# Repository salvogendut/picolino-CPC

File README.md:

# Picolino CPC

A new combined expansion board for the Amstrad CPC, built around a
**Raspberry Pi Pico 2 / RP2350**.

Development branch: `design/pico2-prototype`.
[Implementation issue #1](https://github.com/salvogendut/picolino-CPC/issues/1).

Revision A0 is a **150 × 120 mm, two-layer prototype**. The image is a KiCad
render of the routed design. The W5100S model is a simplified envelope; the
external CH376 module, ribbon cables, shunts and battery cell are not shown.

## Design files

- [KiCad 10 project](hardware/kicad/picolino-cpc.kicad_pro),
  [schematic](hardware/kicad/picolino-cpc.kicad_sch) and
  [PCB](hardware/kicad/picolino-cpc.kicad_pcb).
- [Five-page schematic PDF](hardware/kicad/picolino-cpc-schematic.pdf),
  [BOM](hardware/kicad/bom.csv) and [top assembly drawing](hardware/kicad/picolino-cpc-assembly.svg).
- [3D perspective](docs/images/picolino-cpc-3d.png) and
  [top view](docs/images/picolino-cpc-top.png).
- [Connections, jumper settings and assembly notes](hardware/README.md).

Open the project after cloning the whole repository. Symbols, footprints and
3D models use project-relative paths and are included locally.

| Function | Selected hardware | Intended connection |
| --- | --- | --- |
| ROM emulation | Socketed Pico 2 | CPC memory bus through level translation |
| USB storage | CH376 parallel USB host module | CPC I/O bus, `FE80` / `FE81` |
| Ethernet | **W5100S** parallel module | CPC I/O bus, `FD20`–`FD23` |
| Mouse | PIC16F84A and 74HCT244 | Cyboard mouse interface, `FD10` |
| RTC | Ricoh RP5C01, DIP-18, and CR2032 holder | New nibble-wide RTC interface |
| Address decoding | GAL20V8 and 74HCT21 | Full 16-bit peripheral decoding |

This is the combined-board project. The earlier Cyboard wired POC and its
unfinished RP2040-only carrier are references, not the Picolino PCB.

## Current state

The repository contains the component/compatibility specification, source
provenance, checked interface data, a revised GAL design, the existing PIC mouse
firmware and CH376 diagnostic, and an RP2350-native bus-monitor firmware target.
The monitor deliberately leaves every CPC-facing GPIO as an input. It is a
bring-up tool, **not the completed ROM emulator**.

Revision A uses the reference projects' parallel modules and the original RP5C01
in DIP-18, as confirmed on 2026-10-07. The complete schematic and routed PCB are
included. **This is an untested prototype, not a fabrication release.** Physical
module fit, power sequencing, RTC calibration and CPC bus timing still require
bench validation. Keep both ROM-enable shunts removed with the monitor firmware.
Track implementation in [the design plan](docs/design-plan.md), and read
[the architecture](docs/architecture.md) before connecting hardware.

## Compatibility

- Ethernet and mouse retain the Cyboard register interfaces. Physical regression
  tests remain necessary.
- CH376 uses its own USB-storage protocol; it does not emulate a CF/ATA drive.
- RP5C01 is **not register-compatible with DS12887/Symbiface RTC software**.
  The new driver must read/write 4-bit registers, select banks and handle BCD.
- The inherited PIC firmware speaks **PS/2 mouse protocol**. A USB-shaped mouse
  connector only works with mice supporting that protocol; it is not USB HID.
- Pico 2 needs an RP2350 firmware build. The old RP2040 UF2 and custom linker
  script must not be reused as Pico 2 firmware.

## Software checks

```sh
python3 tools/build_legacy.py --galasm /path/to/galasm --rasm /path/to/rasm
python3 tests/test_decode.py
python3 tests/test_interfaces.py
python3 tests/test_ch376.py   # requires z80==1.0.0
python3 tools/check_hardware.py  # checks the exported KiCad netlist
```

Build the Pico 2 monitor using Pico SDK 2.2.0 and an Arm embedded toolchain:

```sh
cmake -S firmware/pico2 -B build/pico2 -DPICO_BOARD=pico2 \
  -DPICO_SDK_PATH=/path/to/pico-sdk \
  -DPICO_TOOLCHAIN_PATH=/path/to/arm-gnu-toolchain
cmake --build build/pico2 --parallel
```

Use the Arm Cortex-M33 target for this initial revision. Keep hardware ROM enable
off when using the monitor: it never supplies CPC ROM data. USB serial at the
Pico's own USB connector reports bus snapshots and the actual system clock.
The CH376's USB host connector is separate.

See [sources and licensing](docs/sources.md). No CPC OS/BASIC ROMs are included.
Recorded tool versions, results and remaining checks are in
[validation.md](docs/validation.md).

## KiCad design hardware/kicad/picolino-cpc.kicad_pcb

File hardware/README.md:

# Picolino CPC revision A0 hardware

The editable [KiCad 10 project](kicad/picolino-cpc.kicad_pro) contains a cover
sheet and four circuit sheets: bus/power, Pico ROM interface, Ethernet/mouse and
RTC. The PCB is 150 × 120 mm, two copper layers, 1.6 mm nominal thickness, with
four 3.2 mm non-plated mounting holes on a 142 × 112 mm rectangle. Nominal signal
tracks are 0.25 mm; power distribution is 0.80 mm, with pad escapes where needed.
The project minimum is 0.20 mm track/clearance and 0.30 mm drilled vias; routed
vias use 0.70/0.35 mm diameter/drill. Ground pours occupy both layers.

The preview uses Raspberry Pi's official Pico 2 STEP model, local KiCad models,
and an approximate W5100S module envelope. The W5100S connector pad positions
and outline come from Cyboard's EAGLE package; its component heights are
illustrative. Check the actual selected module before manufacture. CH376 is an
external module connected to J2, so it is not included in the rendering.

## Connectors and settings

| Reference | Connection / setting |
| --- | --- |
| J1 | CPC 50-contact expansion through a short, straight-through 50-way ribbon. Pin 1 is marked; check contact numbering at both ends. |
| J2 | Reference parallel CH376 module, 2 × 8 at 2.54 mm, via short straight-through ribbon. Pin 5 supplies fused 5 V; pin 7 is unused. |
| U8 | Cyboard parallel W5100S module, two 1 × 16 sockets, 2.54 mm pitch and 25.4 mm row spacing. RJ45 faces the top edge. |
| U1 | Original Pico 2 with fitted headers; two 1 × 20 sockets, 17.78 mm row spacing. Micro-USB faces the top edge. |
| J4 | PS/2-compatible mouse in a USB-A-shaped socket. This is not a USB HID host. |
| J3 | External **regulated 5 V**: pin 1 positive, pin 2 ground. |
| JP1 | **One shunt only:** 1–2 selects CPC power; 2–3 selects external power. Change only with all power disconnected. |
| JP2 | Both shunts removed: internal CPC ROM and input-only monitor. Fit 1–2 and 3–4 together only with working RP2350 ROM firmware. |
| BT1 | CR2032, positive face up, Keystone 103 holder. No charging circuit. |
| TP1 | RTC ALARM output for calibration/diagnostics; not connected to CPC interrupt. |

J1 contact 40 (`BUSRESET_N`) and contact 41 (`RESET_N`) are separate signals.
The exact contact maps are in [interfaces.json](interfaces.json) and the PDF.
Module orientation must be checked by pin number, not ribbon wire colour.
An SPI-only WIZ810Sio cannot be fitted to U8.

External 5 V is preferred during USB-drive bring-up. JP1 prevents the selected
external supply from feeding CPC 5 V; D1 prevents Pico USB from feeding the
board supply. With external power selected, power the CPC before the board and
turn the board off first: direct peripheral buses are not hot-swap interfaces.
Q1 also disables the Pico translators when CPC 5 V is absent. Measure the full
Pico/module/mouse/USB load before selecting CPC power. F1 protects the CH376
branch, not the whole board; its 500 mA hold rating is not a regulated USB current
limit. Validate USB inrush and voltage drop with the intended drive.

## Assembly

Use the [BOM](kicad/bom.csv) with the [assembly drawing](kicad/picolino-cpc-assembly.svg)
and [schematic PDF](kicad/picolino-cpc-schematic.pdf). The standard passives are
0805; translators are SOIC-20W, supervisor SOIC-8 and Q1 SOT-23. The GAL, PIC,
HCT logic and RTC use DIP sockets. Fit the exact SN74CB3T3245 level-translating
part; an ordinary HC245 or a similarly named bus switch is not equivalent.

Program U2 from the project's GAL source and U9 with the preserved Cyboard PIC
HEX. The Pico firmware currently supplied is an input-only monitor. Leave JP2
open; enabling ROMDIS without a working ROM service prevents normal CPC boot.
Fit one power-selection shunt only. Module sockets and removable shunts are
assembly items in addition to the populated-board BOM. J1 pin 2, U2 pin 12 and
the ground pads of C4/C5 use solid plane connections because surrounding traces
leave insufficient thermal spokes. These joints need adequate soldering heat;
other plane-connected component pads retain thermal reliefs.

U13 is **MAX690AESA+**, with VOUT on pin 1 and battery input on pin 8. Its power
fail output drives the active-high RTC CS input low during backup. WDI is open
to disable the watchdog, PFI is grounded, and PFO is unused. Only the RTC is
battery powered. R20–R30 bias the RTC's bus pins to ground when the board is off.

The original **RP5C01** uses a different oscillator network from RP5C01A:
32.768 kHz crystal, 100 kΩ series resistor, 30 pF at the crystal/resistor node,
56 pF at OSCOUT and an adjustable input load. Use C0G fixed capacitors. Set and
calibrate CV1 using ALARM output mode, avoiding a probe on the crystal pins.
Validate oscillation, trim range, supply transitions and retention current on
the assembled board. The selected crystal needs leads formed to the PCB pitch;
see its BOM note. Verify sourced trimmer and module dimensions before ordering.

## Editing and validation

The native CAD is the reviewable design. `tools/pcb_design.py` records the
circuit and placement; **running `--pcb` replaces all routing**. Preserve manual
edits before regeneration. `--schematic` also regenerates project constraints,
BOM and manifest. `--libraries` needs the KiCad library directory and preserves
the separately supplied Pico STEP model. The module envelope is generated by
`tools/module_model.py`. Routing uses a local Freerouting DSN/SES exchange through
`tools/pcb_route.py`; it does not upload the design to a routing service.
`tools/pcb_finish.py` records the post-route width, edge-clearance, ground-pad
and model corrections for this revision. Its removed-stub UUID belongs to this
particular routing result; review and rerun checks after any new routing pass.

Run from the repository root using KiCad 10:

```sh
kicad-cli sch export netlist hardware/kicad/picolino-cpc.kicad_sch \
  --format kicadxml --output hardware/kicad/checks/netlist.xml
kicad-cli sch erc hardware/kicad/picolino-cpc.kicad_sch --format json \
  --output hardware/kicad/checks/erc.json --exit-code-violations
python3 tools/check_hardware.py
kicad-cli pcb drc hardware/kicad/picolino-cpc.kicad_pcb --format json \
  --output hardware/kicad/checks/drc.json --schematic-parity \
  --refill-zones --save-board --exit-code-violations
```

See [validation](../docs/validation.md) for results and pending bench work,
and [library provenance](kicad/libraries/README.md) for copied assets. No board
has been manufactured or electrically tested. Gerbers are not a release
deliverable at this stage; export them only after reviewing the actual modules,
assembly choices and the outstanding prototype checks.

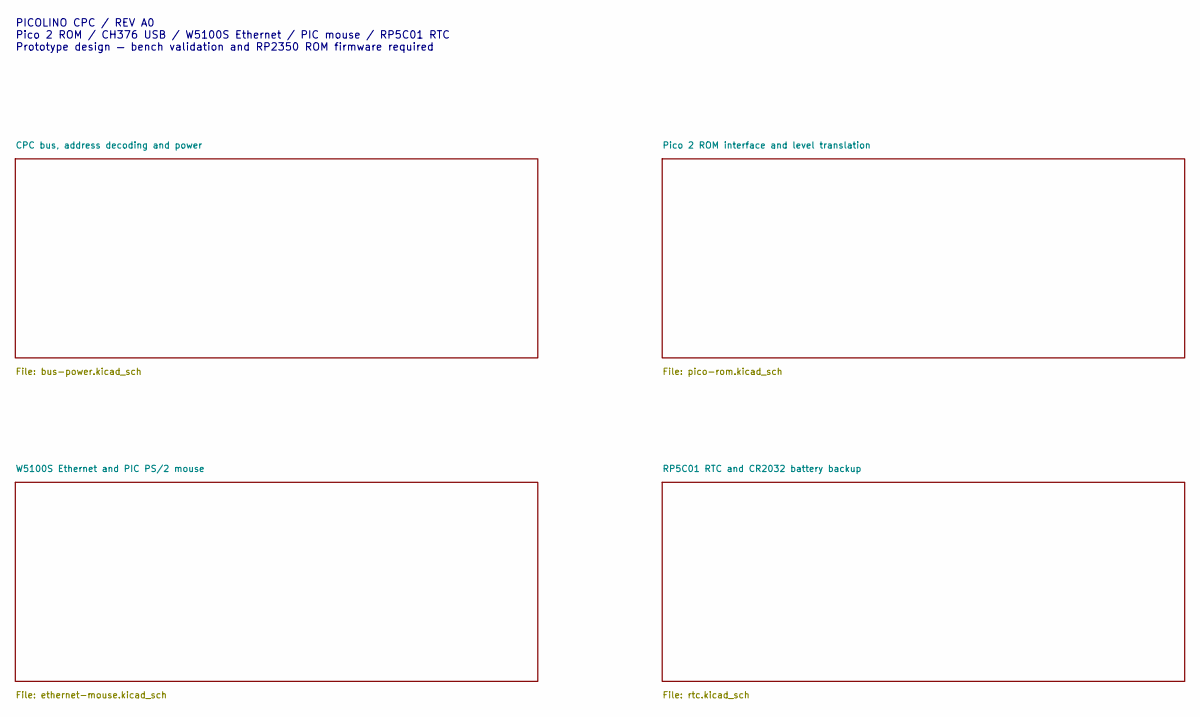
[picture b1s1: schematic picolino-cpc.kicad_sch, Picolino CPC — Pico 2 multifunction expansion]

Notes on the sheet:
PICOLINO CPC / REV A0 Pico 2 ROM / CH376 USB / W5100S Ethernet / PIC mouse / RP5C01 RTC Prototype design — bench validation and RP2350 ROM firmware required

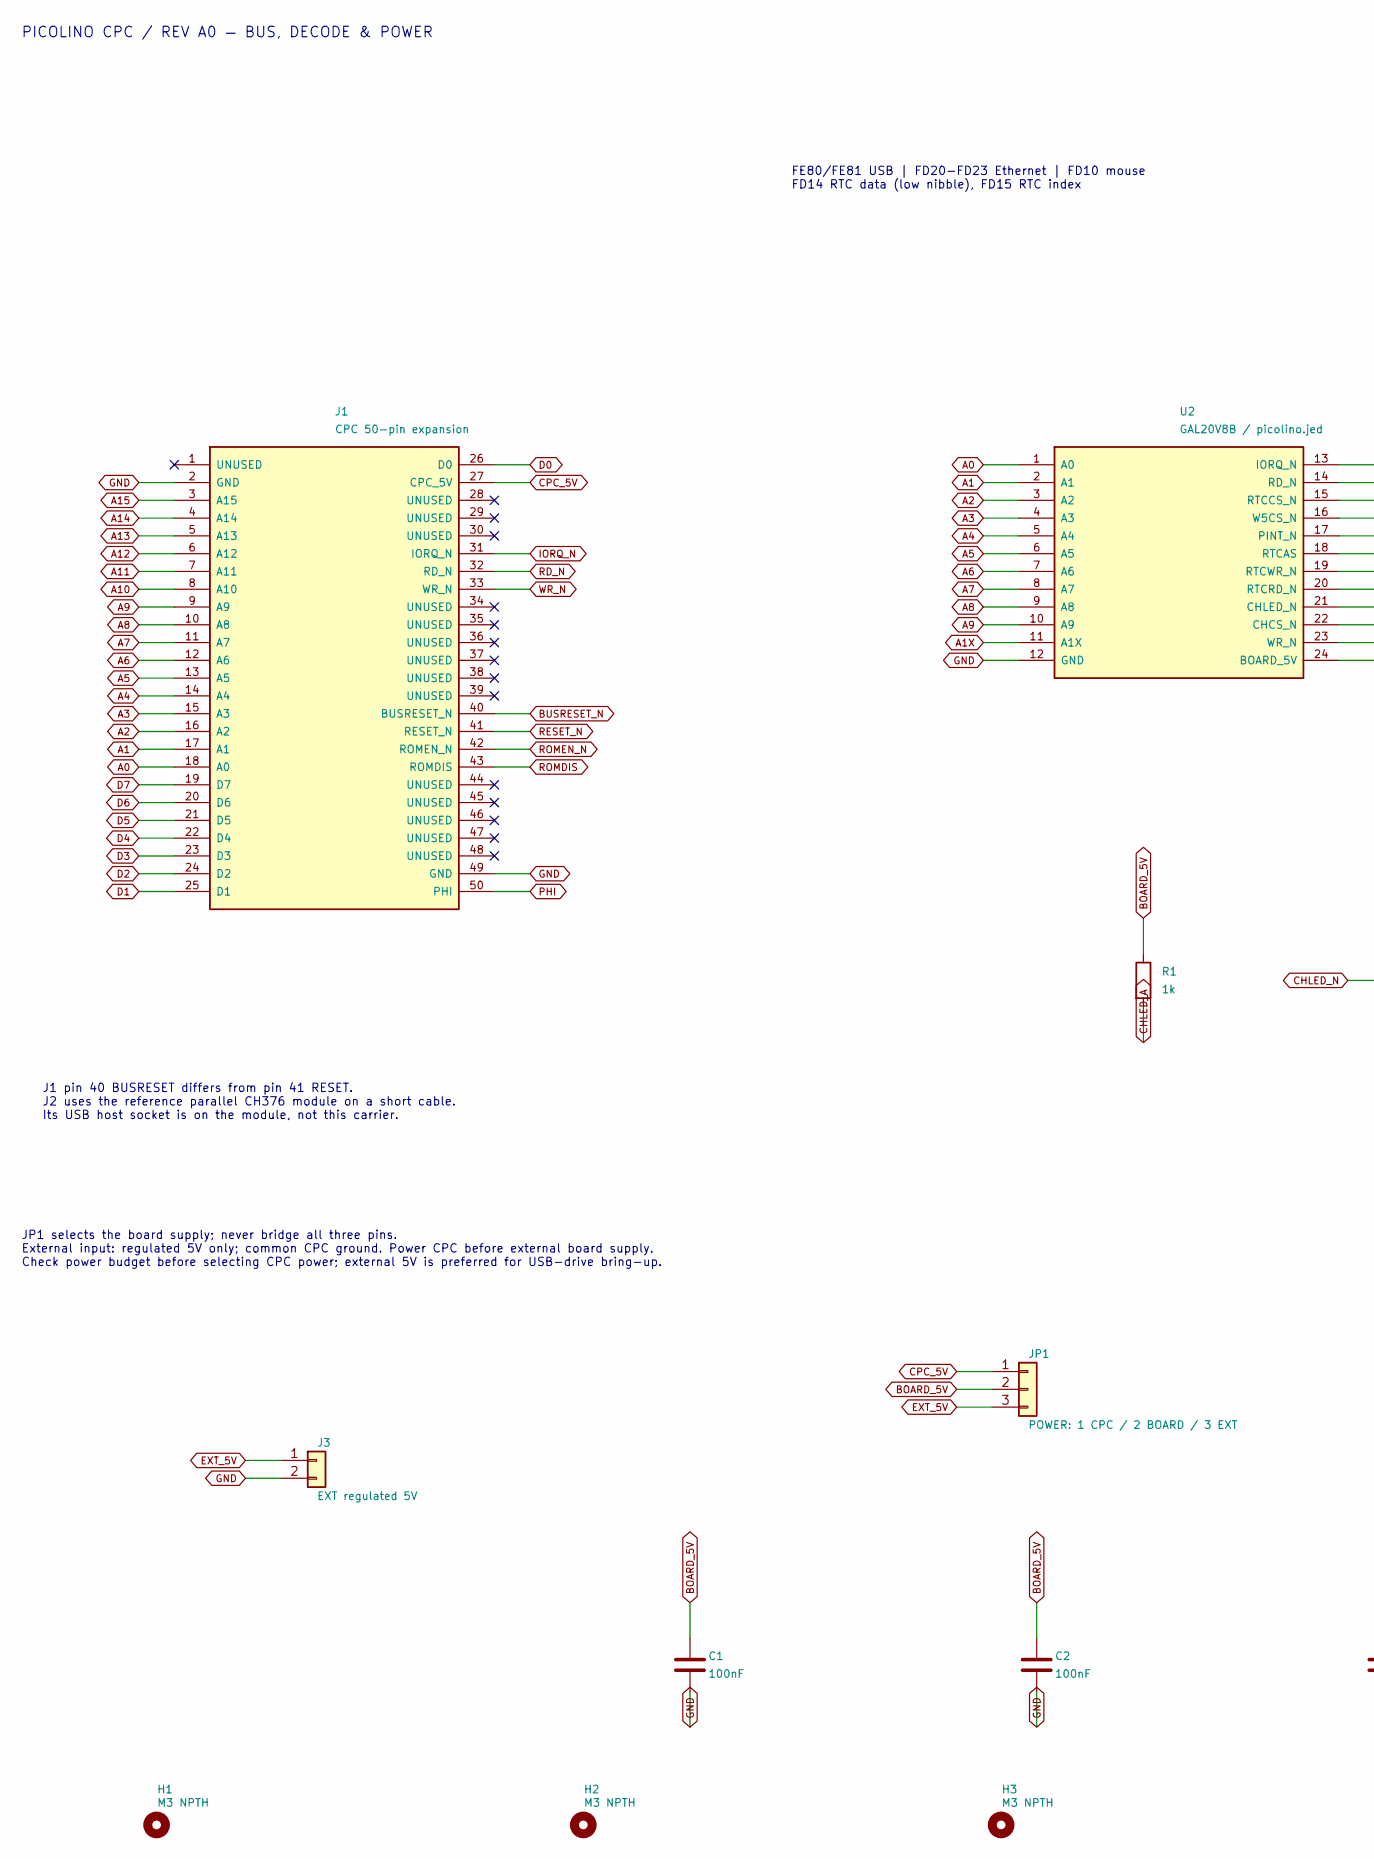
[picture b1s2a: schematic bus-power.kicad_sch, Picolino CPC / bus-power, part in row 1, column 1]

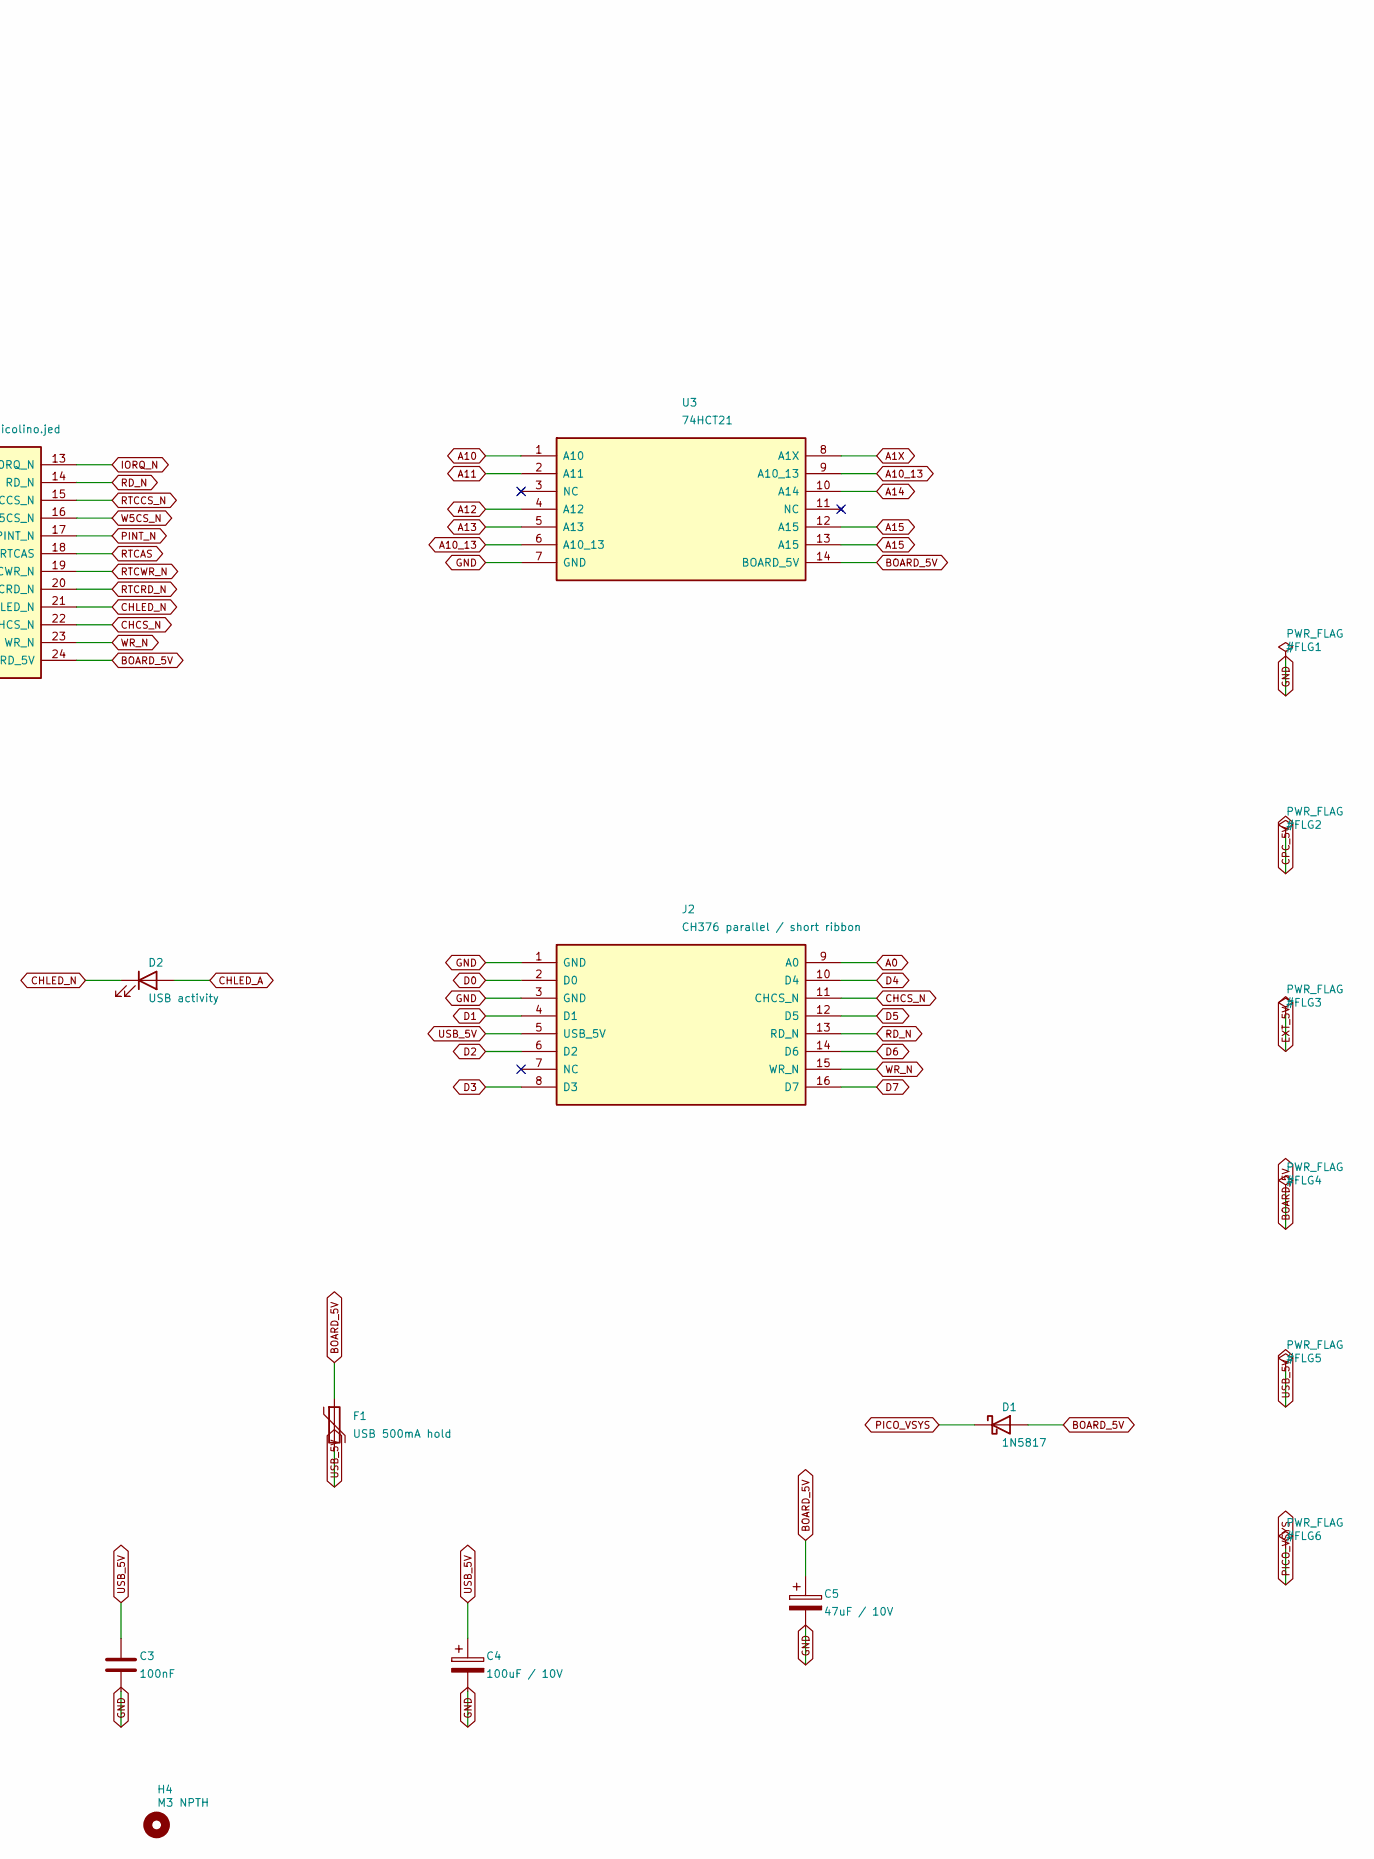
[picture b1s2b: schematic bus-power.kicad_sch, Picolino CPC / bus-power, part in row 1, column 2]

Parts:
C1, C2, C3: 100nF; C_0805_2012Metric
C4: 100uF / 10V; CP_Radial_D6.3mm_P2.50mm
C5: 47uF / 10V; CP_Radial_D5.0mm_P2.00mm
D1: 1N5817; D_DO-41_SOD81_P10.16mm_Horizontal
D2: USB activity; LED_D3.0mm
F1: USB 500mA hold; Fuse_1206_3216Metric
H1, H2, H3, H4: M3 NPTH; MountingHole_3.2mm_M3
J1: CPC 50-pin expansion; IDC-Header_2x25_P2.54mm_Vertical
J2: CH376 parallel / short ribbon; IDC-Header_2x08_P2.54mm_Vertical
J3: EXT regulated 5V; PinHeader_1x02_P2.54mm_Vertical
JP1: POWER: 1 CPC / 2 BOARD / 3 EXT; PinHeader_1x03_P2.54mm_Vertical
R1: 1k; R_0805_2012Metric
U2: GAL20V8B / picolino.jed; DIP-24_W7.62mm_Socket_LongPads
U3: 74HCT21; DIP-14_W7.62mm_Socket_LongPads

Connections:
A0: J1.18 (A0), J2.9 (A0), U2.1 (A0); also elsewhere on the board
A1: J1.17 (A1), U2.2 (A1); also elsewhere on the board
A1X: U2.11 (A1X), U3.8 (A1X)
A2: J1.16 (A2), U2.3 (A2); also elsewhere on the board
A3: J1.15 (A3), U2.4 (A3); also elsewhere on the board
A4: J1.14 (A4), U2.5 (A4); also elsewhere on the board
A5: J1.13 (A5), U2.6 (A5); also elsewhere on the board
A6: J1.12 (A6), U2.7 (A6); also elsewhere on the board
A7: J1.11 (A7), U2.8 (A7); also elsewhere on the board
A8: J1.10 (A8), U2.9 (A8); also elsewhere on the board
A9: J1.9 (A9), U2.10 (A9); also elsewhere on the board
A10: J1.8 (A10), U3.1 (A10); also elsewhere on the board
A10_13: U3.6 (A10_13), U3.9 (A10_13)
A11: J1.7 (A11), U3.2 (A11); also elsewhere on the board
A12: J1.6 (A12), U3.4 (A12); also elsewhere on the board
A13: J1.5 (A13), U3.5 (A13); also elsewhere on the board
A14: J1.4 (A14), U3.10 (A14)
A15: J1.3 (A15), U3.12 (A15), U3.13 (A15); also elsewhere on the board
BOARD_5V: C1.1, C2.1, C5.1, D1.2 (A), F1.1, JP1.2, R1.1, U2.24 (BOARD_5V), U3.14 (BOARD_5V); also elsewhere on the board
BUSRESET_N: J1.40 (BUSRESET_N); also elsewhere on the board
CHCS_N: J2.11 (CHCS_N), U2.22 (CHCS_N)
CHLED_A: D2.2 (A), R1.2
CHLED_N: D2.1 (K), U2.21 (CHLED_N)
CPC_5V: J1.27 (CPC_5V), JP1.1; also elsewhere on the board
D0: J1.26 (D0), J2.2 (D0); also elsewhere on the board
D1: J1.25 (D1), J2.4 (D1); also elsewhere on the board
D2: J1.24 (D2), J2.6 (D2); also elsewhere on the board
D3: J1.23 (D3), J2.8 (D3); also elsewhere on the board
D4: J1.22 (D4), J2.10 (D4); also elsewhere on the board
D5: J1.21 (D5), J2.12 (D5); also elsewhere on the board
D6: J1.20 (D6), J2.14 (D6); also elsewhere on the board
D7: J1.19 (D7), J2.16 (D7); also elsewhere on the board
EXT_5V: J3.1, JP1.3
GND: C1.2, C2.2, C3.2, C4.2, C5.2, J1.2 (GND), J1.49 (GND), J2.1 (GND), J2.3 (GND), J3.2, U2.12 (GND), U3.7 (GND); also elsewhere on the board
IORQ_N: J1.31 (IORQ_N), U2.13 (IORQ_N); also elsewhere on the board
PHI: J1.50 (PHI); also elsewhere on the board
PICO_VSYS: D1.1 (K); also elsewhere on the board
PINT_N: U2.17 (PINT_N); also elsewhere on the board
RD_N: J1.32 (RD_N), J2.13 (RD_N), U2.14 (RD_N); also elsewhere on the board
RESET_N: J1.41 (RESET_N); also elsewhere on the board
ROMDIS: J1.43 (ROMDIS); also elsewhere on the board
ROMEN_N: J1.42 (ROMEN_N); also elsewhere on the board
RTCAS: U2.18 (RTCAS); also elsewhere on the board
RTCCS_N: U2.15 (RTCCS_N); also elsewhere on the board
RTCRD_N: U2.20 (RTCRD_N); also elsewhere on the board
RTCWR_N: U2.19 (RTCWR_N); also elsewhere on the board
USB_5V: C3.1, C4.1, F1.2, J2.5 (USB_5V)
W5CS_N: U2.16 (W5CS_N); also elsewhere on the board
WR_N: J1.33 (WR_N), J2.15 (WR_N), U2.23 (WR_N); also elsewhere on the board

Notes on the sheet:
PICOLINO CPC / REV A0 — BUS, DECODE & POWER
FE80/FE81 USB | FD20-FD23 Ethernet | FD10 mouse FD14 RTC data (low nibble), FD15 RTC index
J1 pin 40 BUSRESET differs from pin 41 RESET. J2 uses the reference parallel CH376 module on a short cable. Its USB host socket is on the module, not this carrier.
JP1 selects the board supply; never bridge all three pins. External input: regulated 5V only; common CPC ground. Power CPC before external board supply. Check power budget before selecting CPC power; external 5V is preferred for USB-drive bring-up.

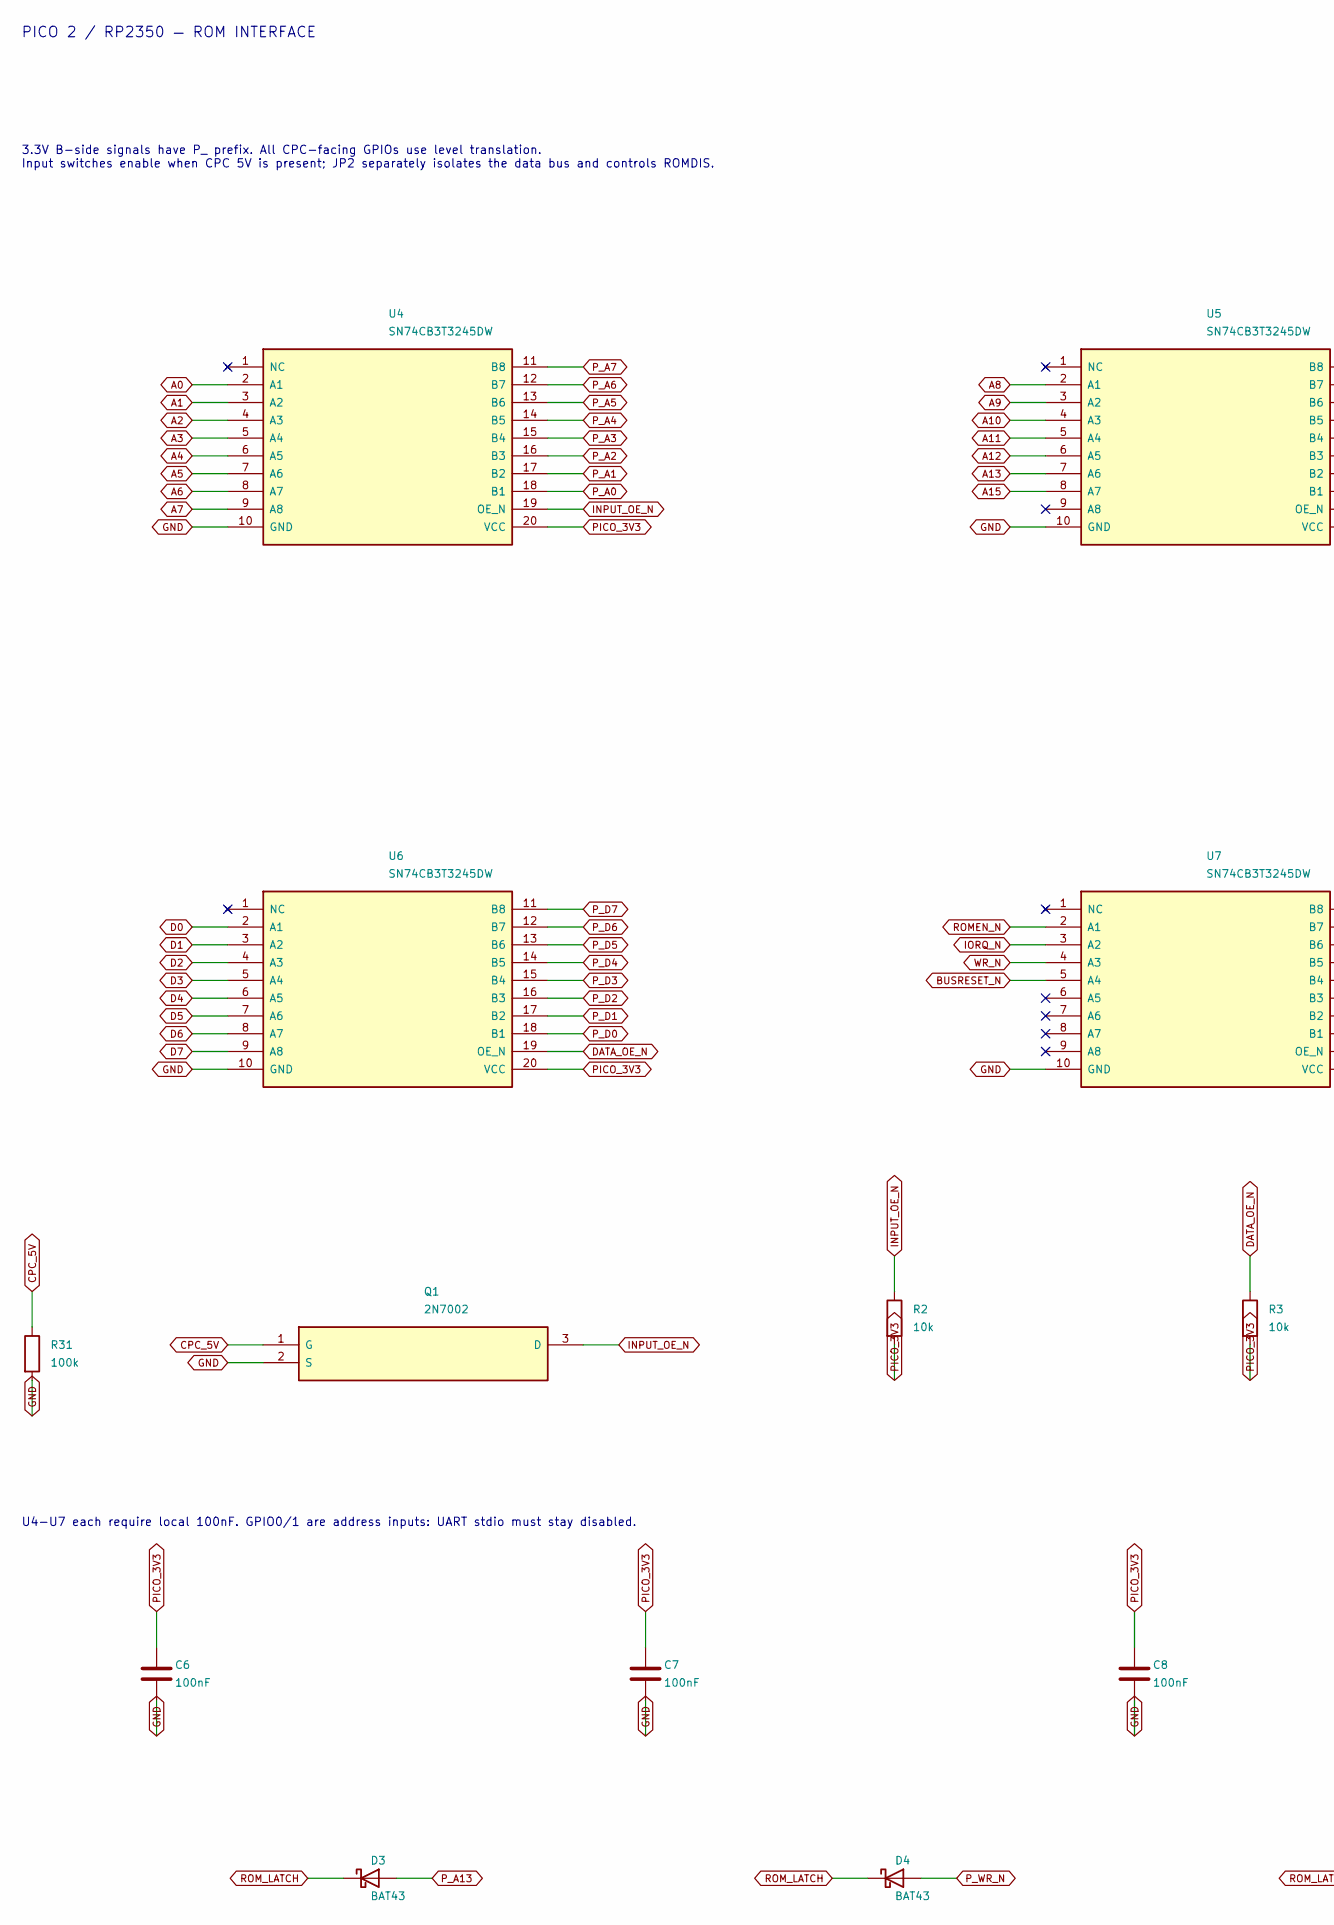
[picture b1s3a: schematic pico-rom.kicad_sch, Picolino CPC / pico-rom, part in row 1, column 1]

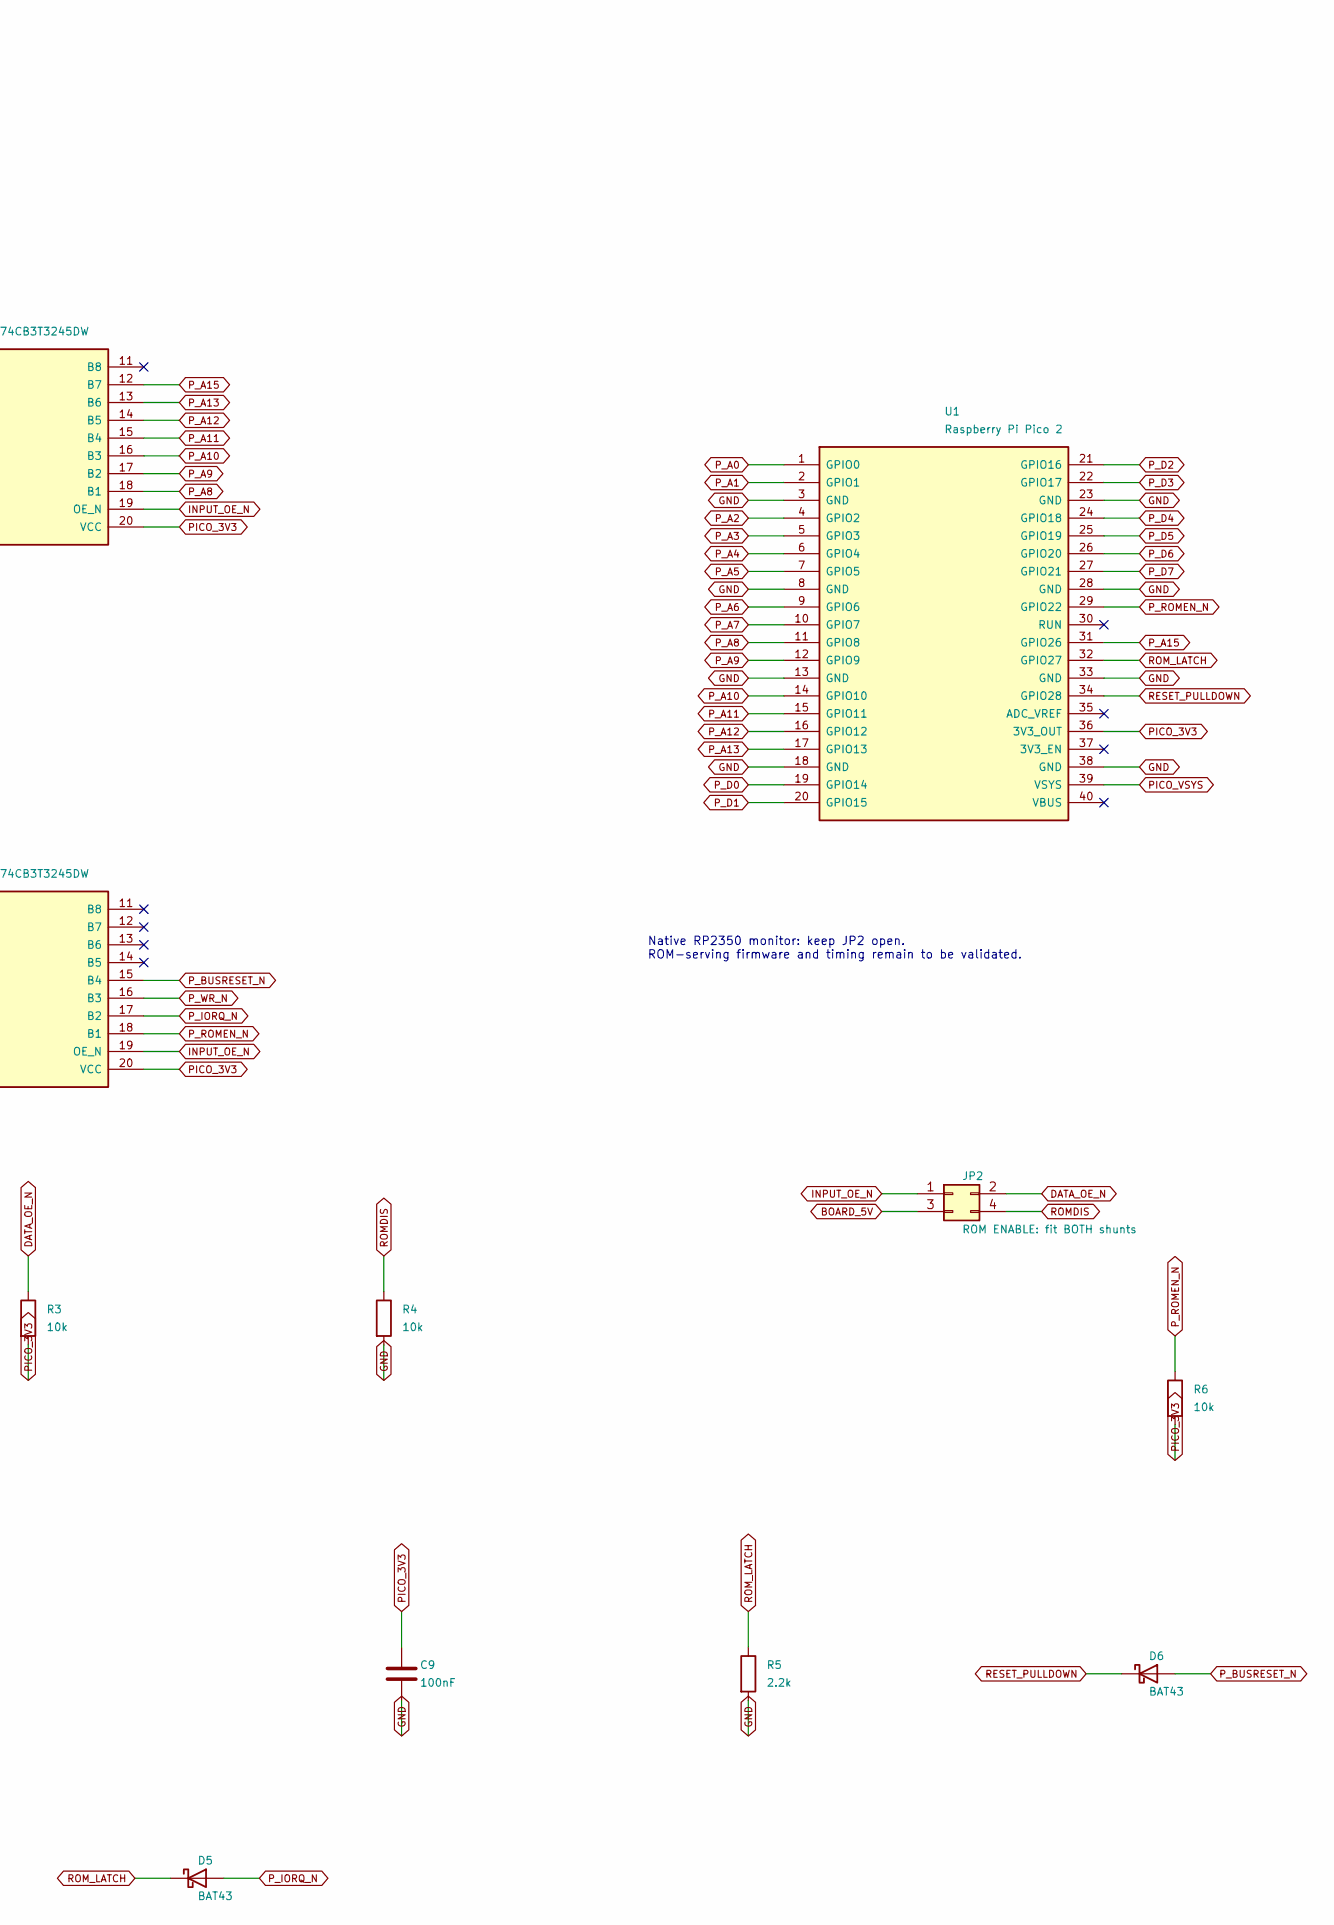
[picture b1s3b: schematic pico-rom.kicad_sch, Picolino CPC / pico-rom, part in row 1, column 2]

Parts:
C6, C7, C8, C9: 100nF; C_0805_2012Metric
D3, D4, D5, D6: BAT43; D_DO-35_SOD27_P7.62mm_Horizontal
JP2: ROM ENABLE: fit BOTH shunts; PinHeader_2x02_P2.54mm_Vertical
Q1: 2N7002; SOT-23
R2, R3, R4, R6: 10k; R_0805_2012Metric
R5: 2.2k; R_0805_2012Metric
R31: 100k; R_0805_2012Metric
U1: Raspberry Pi Pico 2; Pico2_Socketed
U4, U5, U6, U7: SN74CB3T3245DW; SOIC-20W_7.5x12.8mm_P1.27mm

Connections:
A0: U4.2 (A1); also elsewhere on the board
A1: U4.3 (A2); also elsewhere on the board
A2: U4.4 (A3); also elsewhere on the board
A3: U4.5 (A4); also elsewhere on the board
A4: U4.6 (A5); also elsewhere on the board
A5: U4.7 (A6); also elsewhere on the board
A6: U4.8 (A7); also elsewhere on the board
A7: U4.9 (A8); also elsewhere on the board
A8: U5.2 (A1); also elsewhere on the board
A9: U5.3 (A2); also elsewhere on the board
A10: U5.4 (A3); also elsewhere on the board
A11: U5.5 (A4); also elsewhere on the board
A12: U5.6 (A5); also elsewhere on the board
A13: U5.7 (A6); also elsewhere on the board
A15: U5.8 (A7); also elsewhere on the board
BOARD_5V: JP2.3; also elsewhere on the board
BUSRESET_N: U7.5 (A4); also elsewhere on the board
CPC_5V: Q1.1 (G), R31.1; also elsewhere on the board
D0: U6.2 (A1); also elsewhere on the board
D1: U6.3 (A2); also elsewhere on the board
D2: U6.4 (A3); also elsewhere on the board
D3: U6.5 (A4); also elsewhere on the board
D4: U6.6 (A5); also elsewhere on the board
D5: U6.7 (A6); also elsewhere on the board
D6: U6.8 (A7); also elsewhere on the board
D7: U6.9 (A8); also elsewhere on the board
DATA_OE_N: JP2.2, R3.1, U6.19 (OE_N)
GND: C6.2, C7.2, C8.2, C9.2, Q1.2 (S), R4.2, R5.2, R31.2, U1.3 (GND), U1.8 (GND), U1.13 (GND), U1.18 (GND), U1.23 (GND), U1.28 (GND), U1.33 (GND), U1.38 (GND), U4.10 (GND), U5.10 (GND), U6.10 (GND), U7.10 (GND); also elsewhere on the board
INPUT_OE_N: JP2.1, Q1.3 (D), R2.1, U4.19 (OE_N), U5.19 (OE_N), U7.19 (OE_N)
IORQ_N: U7.3 (A2); also elsewhere on the board
PICO_3V3: C6.1, C7.1, C8.1, C9.1, R2.2, R3.2, R6.2, U1.36 (3V3_OUT), U4.20 (VCC), U5.20 (VCC), U6.20 (VCC), U7.20 (VCC)
PICO_VSYS: U1.39 (VSYS); also elsewhere on the board
P_A0: U1.1 (GPIO0), U4.18 (B1)
P_A1: U1.2 (GPIO1), U4.17 (B2)
P_A2: U1.4 (GPIO2), U4.16 (B3)
P_A3: U1.5 (GPIO3), U4.15 (B4)
P_A4: U1.6 (GPIO4), U4.14 (B5)
P_A5: U1.7 (GPIO5), U4.13 (B6)
P_A6: U1.9 (GPIO6), U4.12 (B7)
P_A7: U1.10 (GPIO7), U4.11 (B8)
P_A8: U1.11 (GPIO8), U5.18 (B1)
P_A9: U1.12 (GPIO9), U5.17 (B2)
P_A10: U1.14 (GPIO10), U5.16 (B3)
P_A11: U1.15 (GPIO11), U5.15 (B4)
P_A12: U1.16 (GPIO12), U5.14 (B5)
P_A13: D3.2 (A), U1.17 (GPIO13), U5.13 (B6)
P_A15: U1.31 (GPIO26), U5.12 (B7)
P_BUSRESET_N: D6.2 (A), U7.15 (B4)
P_D0: U1.19 (GPIO14), U6.18 (B1)
P_D1: U1.20 (GPIO15), U6.17 (B2)
P_D2: U1.21 (GPIO16), U6.16 (B3)
P_D3: U1.22 (GPIO17), U6.15 (B4)
P_D4: U1.24 (GPIO18), U6.14 (B5)
P_D5: U1.25 (GPIO19), U6.13 (B6)
P_D6: U1.26 (GPIO20), U6.12 (B7)
P_D7: U1.27 (GPIO21), U6.11 (B8)
P_IORQ_N: D5.2 (A), U7.17 (B2)
P_ROMEN_N: R6.1, U1.29 (GPIO22), U7.18 (B1)
P_WR_N: D4.2 (A), U7.16 (B3)
RESET_PULLDOWN: D6.1 (K), U1.34 (GPIO28)
ROMDIS: JP2.4, R4.1; also elsewhere on the board
ROMEN_N: U7.2 (A1); also elsewhere on the board
ROM_LATCH: D3.1 (K), D4.1 (K), D5.1 (K), R5.1, U1.32 (GPIO27)
WR_N: U7.4 (A3); also elsewhere on the board

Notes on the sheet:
PICO 2 / RP2350 — ROM INTERFACE
3.3V B-side signals have P_ prefix. All CPC-facing GPIOs use level translation. Input switches enable when CPC 5V is present; JP2 separately isolates the data bus and controls ROMDIS.
Native RP2350 monitor: keep JP2 open. ROM-serving firmware and timing remain to be validated.
U4-U7 each require local 100nF. GPIO0/1 are address inputs: UART stdio must stay disabled.
